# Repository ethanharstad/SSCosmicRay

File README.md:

SSCosmicRay
===========
[Hackaday Project Log](http://hackaday.io/project/2998-Solid-State-Cosmic-Ray-Detector)

Cosmic ray detectors are a common physics experiment and frequently flown on balloons to measure the change in cosmic ray flux with altitude.
These experiments are typically performed with off the shelf Geiger–Müller tube based detectors. G-M tubes are typically quite expensive and involve high voltages which can become difficult to manage in the near vacuum experienced with high altitude balloons.
A reverse biased photodiode can be used in much the same way as a G-M tube but with lower cost, lower voltage, almost no dead time, and the additional benefit of an output voltage proportional to the radiation energy. 

Inspired by a Maxim [application note](http://www.maximintegrated.com/en/app-notes/index.mvp/id/2236).

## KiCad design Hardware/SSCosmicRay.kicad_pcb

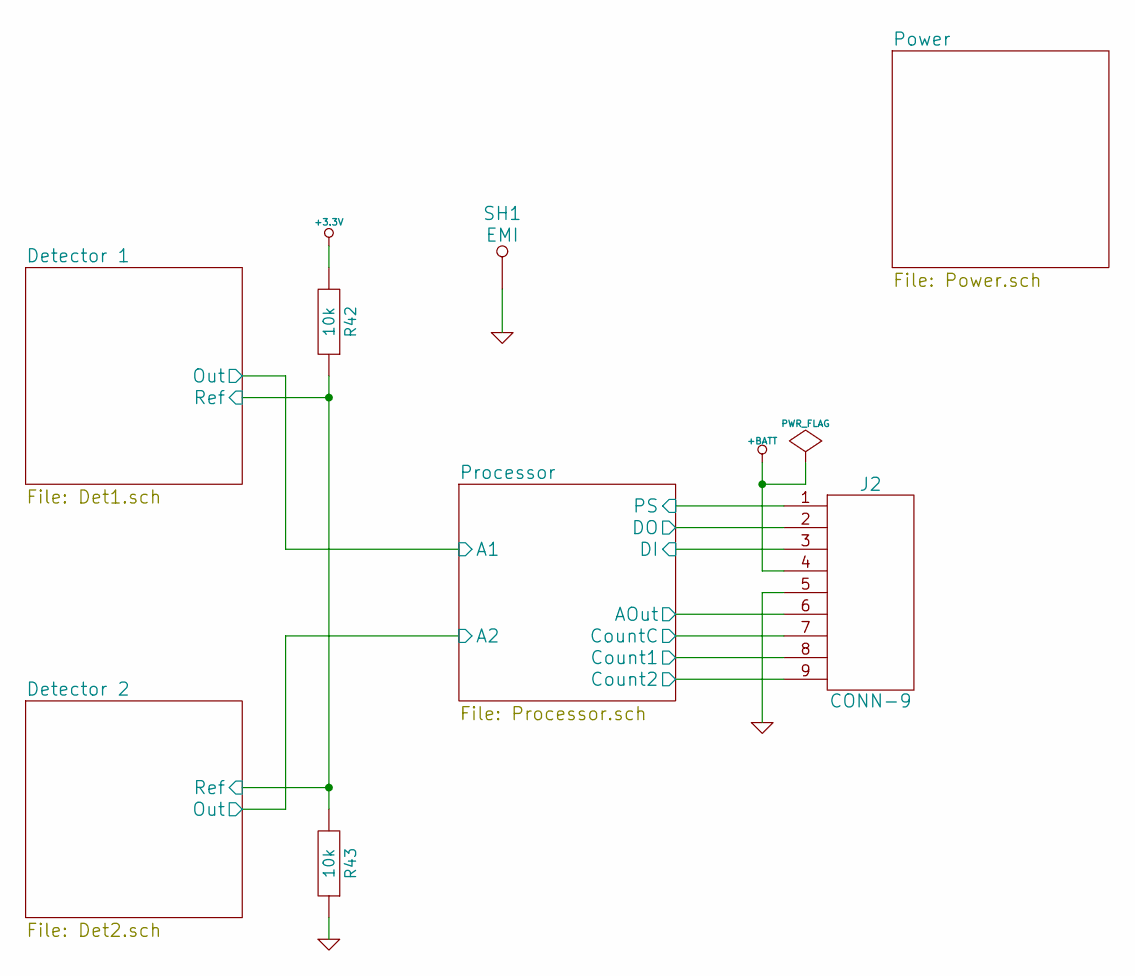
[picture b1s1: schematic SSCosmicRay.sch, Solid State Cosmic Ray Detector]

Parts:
J2: CONN-9; MFR Part No 1734354-2
R42, R43: 10k; RESC1608; Tolerance 1%; MFR Part No RC0603FR-0710KL
SH1: EMI

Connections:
+3.3V: R42.2; also elsewhere on the board
+BATT: J2.4; also elsewhere on the board
/Detector 1/Ref: R42.1, R43.2; also elsewhere on the board
/Processor/AOut: J2.6; also elsewhere on the board
/Processor/Count1: J2.8; also elsewhere on the board
/Processor/Count2: J2.9; also elsewhere on the board
/Processor/CountC: J2.7; also elsewhere on the board
/Processor/DI: J2.3; also elsewhere on the board
/Processor/DO: J2.2; also elsewhere on the board
/Processor/PS: J2.1; also elsewhere on the board
GND: J2.5, R43.1, SH1.1; also elsewhere on the board

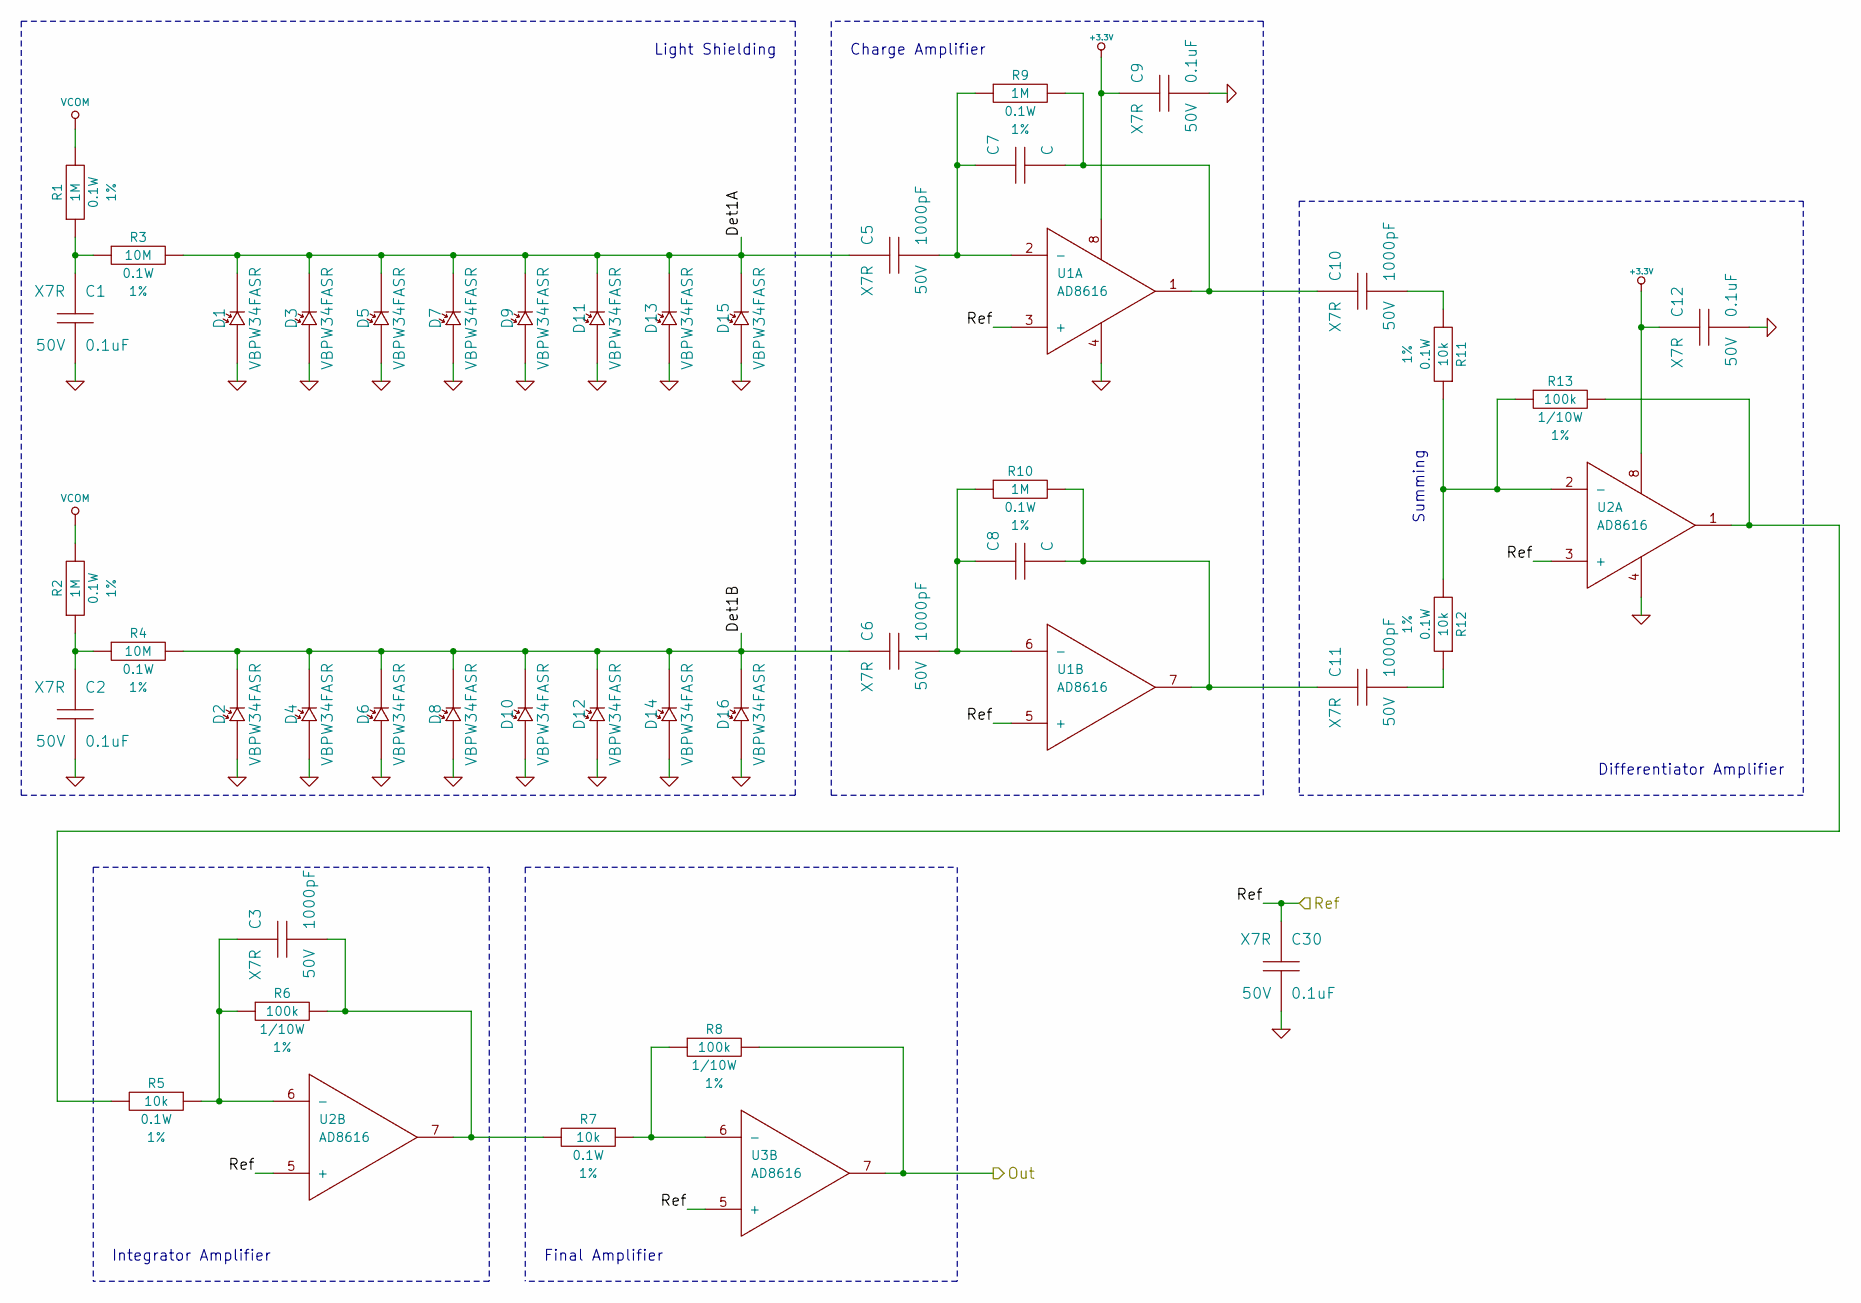
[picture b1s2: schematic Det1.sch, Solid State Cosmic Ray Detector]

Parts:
C1, C2, C9, C12, C30: 0.1uF; CAPC1608; Voltage 50V; MFR Part No CL10B104KB8SFNC
C3, C5, C6, C10, C11: 1000pF; CAPC1608; Voltage 50V; MFR Part No CL10B102KB8SFNC
C7, C8: C; Voltage V
D1, D2, D3, D4, D5, D6, D7, D8, D9, D10, D11, D12, D13, D14, D15, D16: VBPW34FASR; DIOC-BPW34R; MFR Part No VBPW34FASR
R1, R2, R9, R10: 1M; RESC1608; Tolerance 1%; MFR Part No RC0603FR-071ML
R3, R4: 10M; RESC1608; Tolerance 1%; MFR Part No RC0603FR-0710ML
R5, R7, R11, R12: 10k; RESC1608; Tolerance 1%; MFR Part No RC0603FR-0710KL
R6, R8, R13: 100k; Tolerance 1%; MFR Part No RC0603FR-07100KL
U1, U2, U3: AD8616; MFR Part No AD8616ARMZ-REEL

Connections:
+3.3V: C9.1, C12.1, U1.8, U2.8; also elsewhere on the board
/Detector 1/Det1A: C5.1, D1.2, D3.2, D5.2, D7.2, D9.2, D11.2, D13.2, D15.2, R3.2
/Detector 1/Det1B: C6.1, D2.2, D4.2, D6.2, D8.2, D10.2, D12.2, D14.2, D16.2, R4.2
/Detector 1/Ref: C30.1, U1.3 (+), U1.5 (+), U2.3 (+), U2.5 (+), U3.5 (+); also elsewhere on the board
/Processor/A1: R8.2, U3.7; also elsewhere on the board
GND: C1.2, C2.2, C9.2, C12.2, C30.2, D1.1, D2.1, D3.1, D4.1, D5.1, D6.1, D7.1, D8.1, D9.1, D10.1, D11.1, D12.1, D13.1, D14.1, D15.1, D16.1, U1.4, U2.4; also elsewhere on the board
unnamed: C8.2, C11.1, R10.2, U1.7
unnamed: C11.2, R12.1
unnamed: C10.2, R11.2
unnamed: C3.2, R6.2, R7.2, U2.7
unnamed: C7.2, C10.1, R9.2, U1.1
unnamed: R11.1, R12.2, R13.1, U2.2 (-)
unnamed: R7.1, R8.1, U3.6 (-)
unnamed: C3.1, R5.1, R6.1, U2.6 (-)
unnamed: R5.2, R13.2, U2.1
unnamed: C6.2, C8.1, R10.1, U1.6 (-)
unnamed: C5.2, C7.1, R9.1, U1.2 (-)
unnamed: C2.1, R2.1, R4.1
unnamed: C1.1, R1.1, R3.1
VCOM: R1.2, R2.2; also elsewhere on the board

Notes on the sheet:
Charge Amplifier
Differentiator Amplifier
Integrator Amplifier
Summing
Light Shielding
Final Amplifier

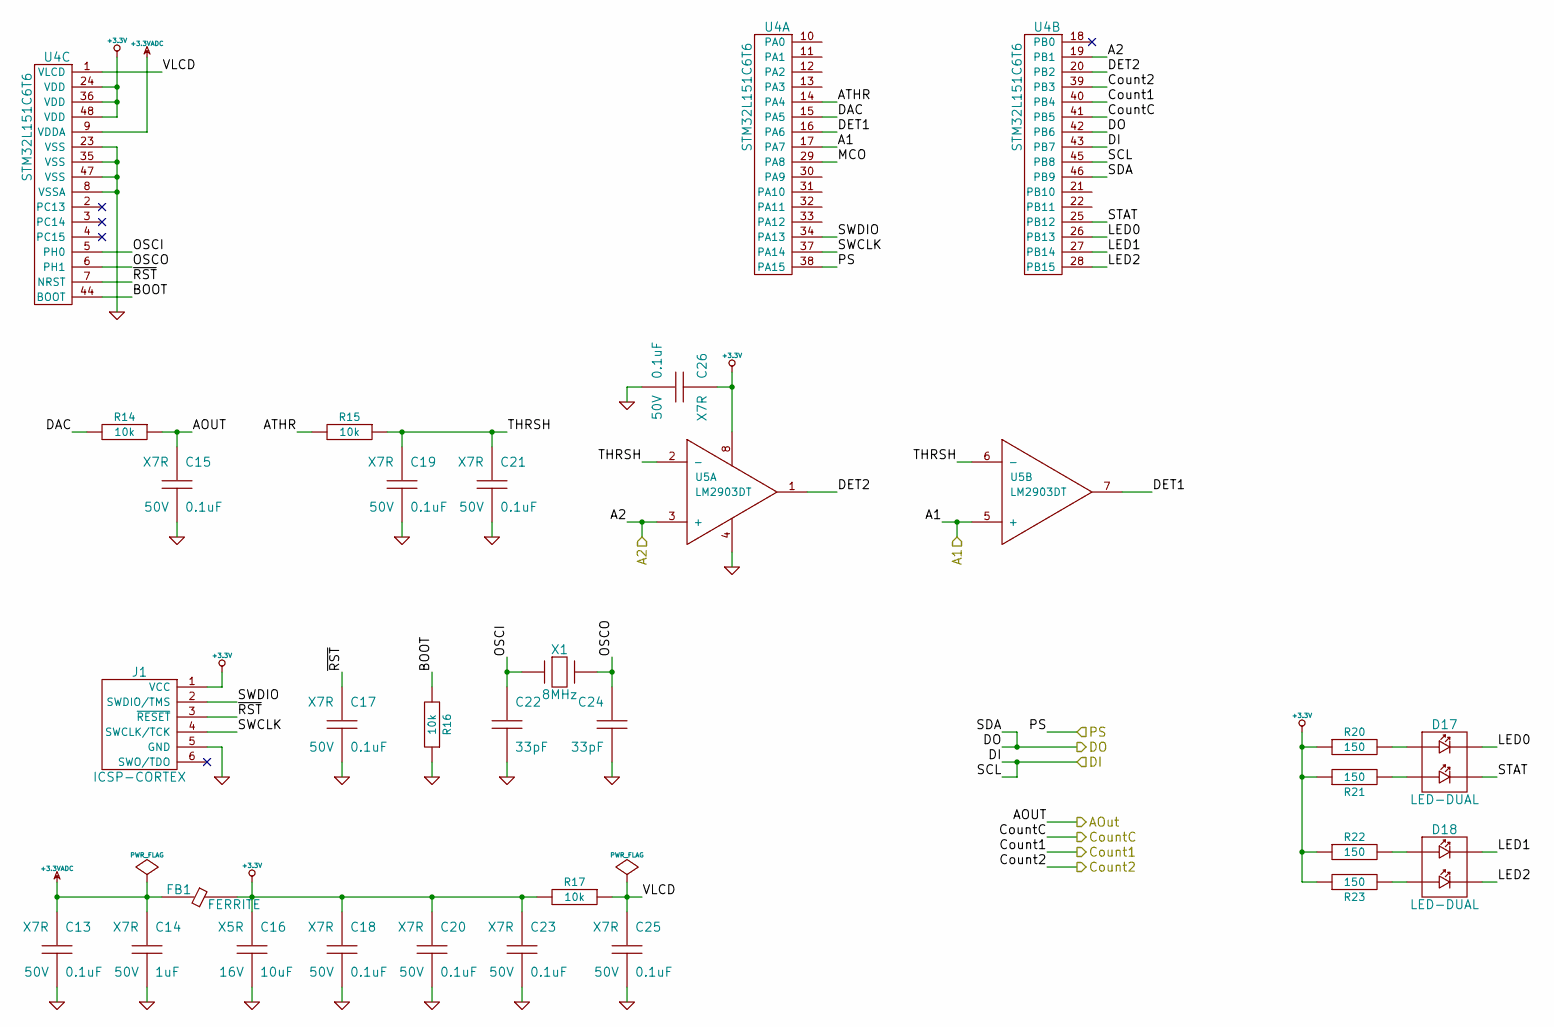
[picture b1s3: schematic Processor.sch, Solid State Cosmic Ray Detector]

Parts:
C13, C15, C17, C18, C19, C20, C21, C23, C25, C26: 0.1uF; CAPC1608; Voltage 50V; MFR Part No CL10B104KB8SFNC
C14: 1uF; CAPC1608; Voltage 50V; MFR Part No CL21B105KBFNNNE
C16: 10uF; CAPC2012; Voltage 16V; MFR Part No EMK212BJ106KG-T
C22, C24: 33pF; Voltage 50V; MFR Part No C0603C330J5GACTU
D17: LED-DUAL; Voltage V; MFR Part No 553-0121F
D18: LED-DUAL; Voltage V; MFR Part No 553-0122F
FB1: FERRITE
J1: ICSP-CORTEX
R14, R15, R16, R17: 10k; RESC1608; Tolerance 1%; MFR Part No RC0603FR-0710KL
R20, R21, R22, R23: 150; RESC1608; Tolerance %; MFR Part No RMCF0603FT150R
U4: STM32L151C6T6; MFR Part No STM32L151C6T6
U5: LM2903DT; MFR Part No LM2903DGKR
X1: 8MHz; MFR Part No ABM7-8.000MHZ-D2Y-T

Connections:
+3.3V: C16.1, C18.1, C20.1, C23.1, C26.1, FB1.2, J1.1 (VCC), R17.2, R20.1, R21.1, R22.1, R23.1, U4.24 (VDD), U4.36 (VDD), U4.48 (VDD), U5.8; also elsewhere on the board
+3.3VADC: C13.1, C14.1, FB1.1, U4.9 (VDDA)
/Processor/A1: U4.17 (PA7), U5.5 (+); also elsewhere on the board
/Processor/A2: U4.19 (PB1), U5.3 (+); also elsewhere on the board
/Processor/AOut: C15.1, R14.1; also elsewhere on the board
/Processor/ATHR: R15.2, U4.14 (PA4)
/Processor/BOOT: R16.2, U4.44 (BOOT)
/Processor/Count1: U4.40 (PB4); also elsewhere on the board
/Processor/Count2: U4.39 (PB3); also elsewhere on the board
/Processor/CountC: U4.41 (PB5); also elsewhere on the board
/Processor/DAC: R14.2, U4.15 (PA5)
/Processor/DET1: U4.16 (PA6), U5.7
/Processor/DET2: U4.20 (PB2), U5.1
/Processor/DI: U4.43 (PB7), U4.45 (PB8); also elsewhere on the board
/Processor/DO: U4.42 (PB6), U4.46 (PB9); also elsewhere on the board
/Processor/LED0: D17.2, U4.26 (PB13)
/Processor/LED1: D18.2, U4.27 (PB14)
/Processor/LED2: D18.4, U4.28 (PB15)
/Processor/OSCI: C22.1, U4.5 (PH0), X1.1
/Processor/OSCO: C24.1, U4.6 (PH1), X1.2
/Processor/PS: U4.38 (PA15); also elsewhere on the board
/Processor/STAT: D17.4, U4.25 (PB12)
/Processor/SWCLK: J1.4 (SWCLK/TCK), U4.37 (PA14)
/Processor/SWDIO: J1.2 (SWDIO/TMS), U4.34 (PA13)
/Processor/THRSH: C19.1, C21.1, R15.1, U5.2 (-), U5.6 (-)
/Processor/VLCD: C25.1, R17.1, U4.1 (VLCD)
/Processor/~RST: C17.1, J1.3 (~RESET), U4.7 (NRST)
GND: C13.2, C14.2, C15.2, C16.2, C17.2, C18.2, C19.2, C20.2, C21.2, C22.2, C23.2, C24.2, C25.2, C26.2, J1.5 (GND), R16.1, U4.8 (VSSA), U4.23 (VSS), U4.35 (VSS), U4.47 (VSS), U5.4; also elsewhere on the board
unnamed: D18.3, R23.2
unnamed: D18.1, R22.2
unnamed: D17.3, R21.2
unnamed: D17.1, R20.2

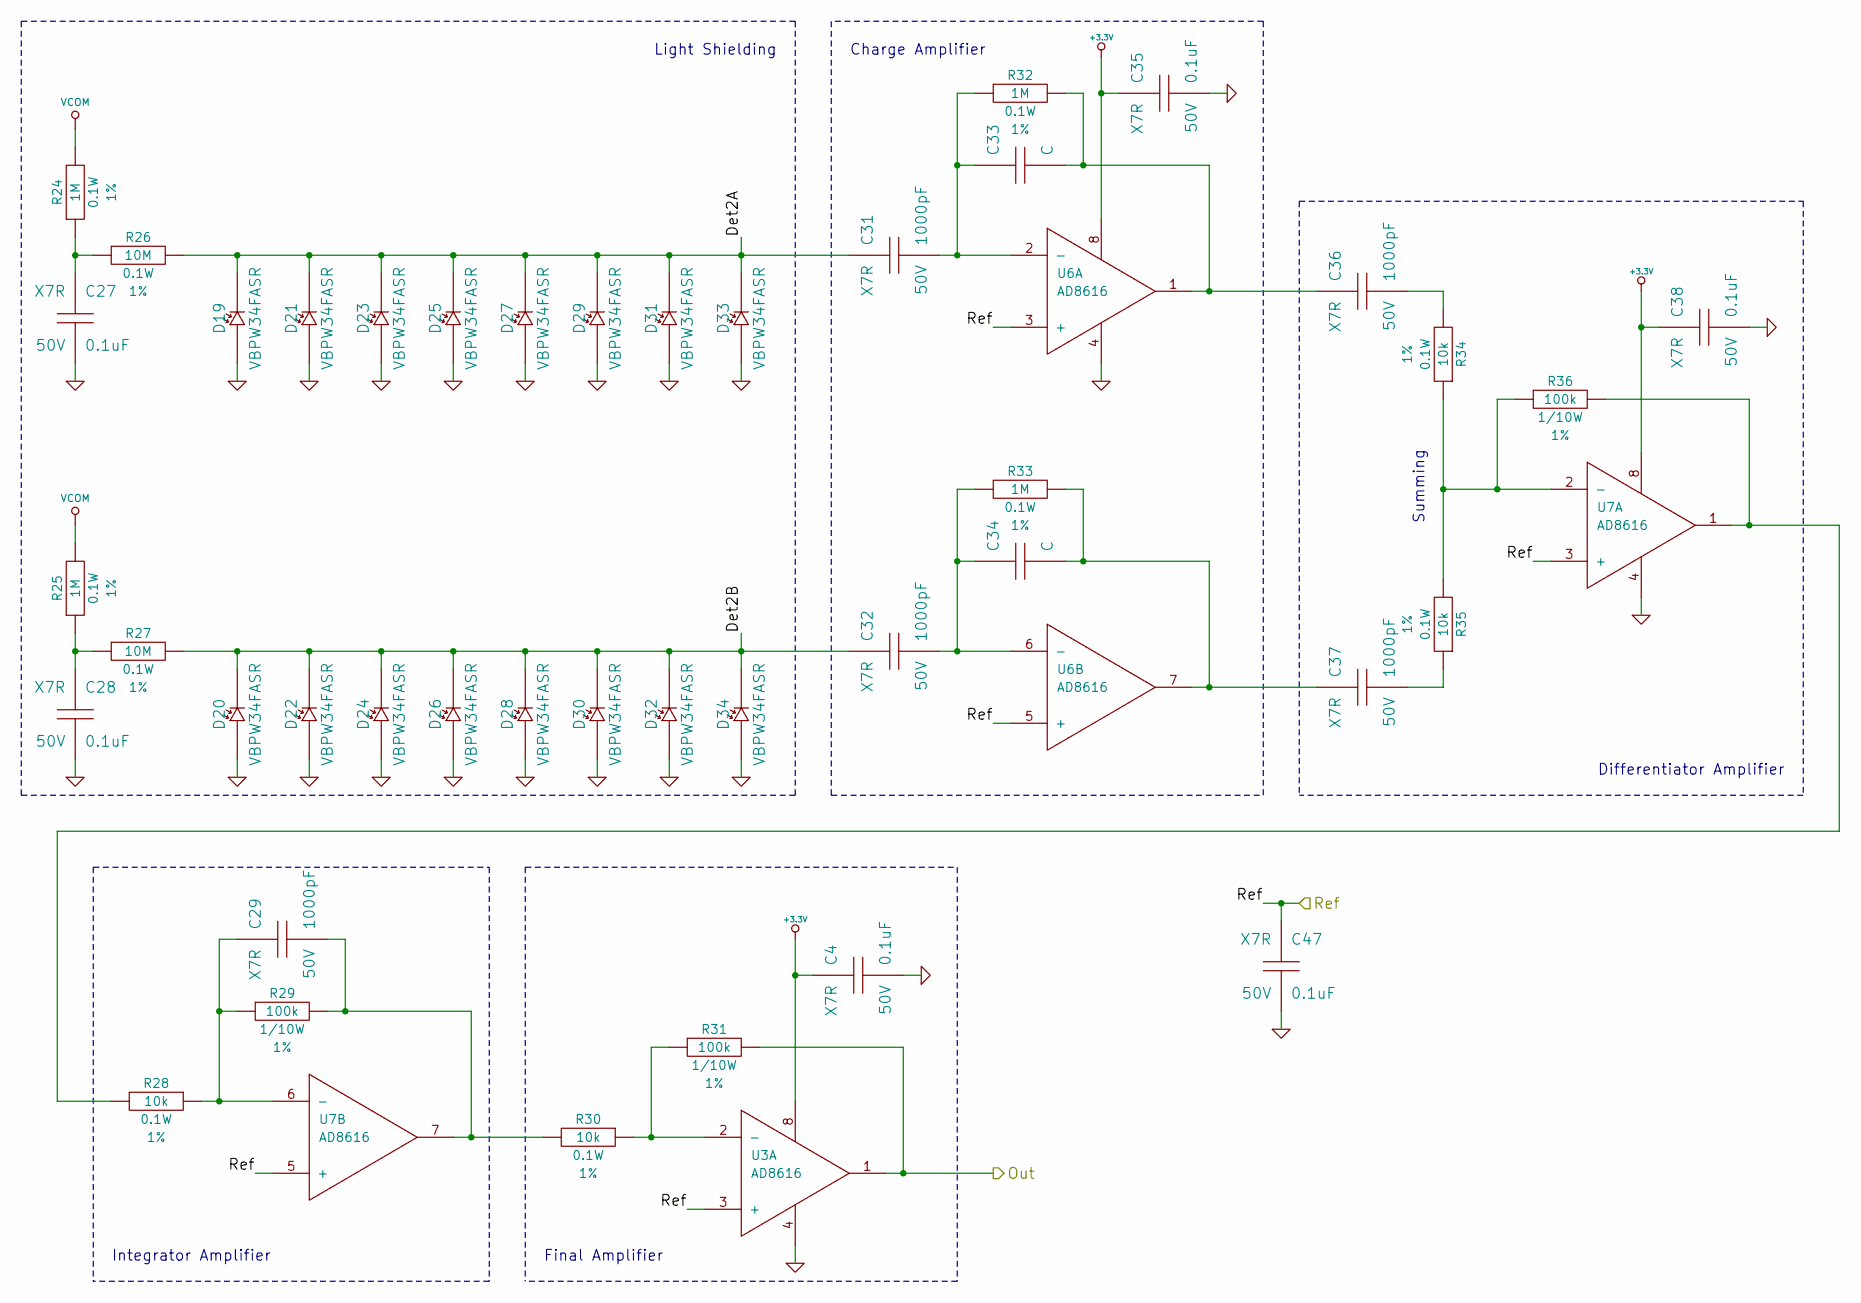
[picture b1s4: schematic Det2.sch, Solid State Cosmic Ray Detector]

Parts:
C4, C27, C28, C35, C38, C47: 0.1uF; CAPC1608; Voltage 50V; MFR Part No CL10B104KB8SFNC
C29, C31, C32, C36, C37: 1000pF; CAPC1608; Voltage 50V; MFR Part No CL10B102KB8SFNC
C33, C34: C; Voltage V
D19, D20, D21, D22, D23, D24, D25, D26, D27, D28, D29, D30, D31, D32, D33, D34: VBPW34FASR; DIOC-BPW34R; MFR Part No VBPW34FASR
R24, R25, R32, R33: 1M; RESC1608; Tolerance 1%; MFR Part No RC0603FR-071ML
R26, R27: 10M; RESC1608; Tolerance 1%; MFR Part No RC0603FR-0710ML
R28, R30, R34, R35: 10k; RESC1608; Tolerance 1%; MFR Part No RC0603FR-0710KL
R29, R31, R36: 100k; Tolerance 1%; MFR Part No RC0603FR-07100KL
U3, U6, U7: AD8616; MFR Part No AD8616ARMZ-REEL

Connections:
+3.3V: C4.1, C35.1, C38.1, U3.8, U6.8, U7.8; also elsewhere on the board
/Detector 1/Ref: C47.1, U3.3 (+), U6.3 (+), U6.5 (+), U7.3 (+), U7.5 (+); also elsewhere on the board
/Detector 2/Det2A: C31.1, D19.2, D21.2, D23.2, D25.2, D27.2, D29.2, D31.2, D33.2, R26.2
/Detector 2/Det2B: C32.1, D20.2, D22.2, D24.2, D26.2, D28.2, D30.2, D32.2, D34.2, R27.2
/Processor/A2: R31.2, U3.1; also elsewhere on the board
GND: C4.2, C27.2, C28.2, C35.2, C38.2, C47.2, D19.1, D20.1, D21.1, D22.1, D23.1, D24.1, D25.1, D26.1, D27.1, D28.1, D29.1, D30.1, D31.1, D32.1, D33.1, D34.1, U3.4, U6.4, U7.4; also elsewhere on the board
unnamed: C29.1, R28.1, R29.1, U7.6 (-)
unnamed: C37.2, R35.1
unnamed: C29.2, R29.2, R30.2, U7.7
unnamed: C34.2, C37.1, R33.2, U6.7
unnamed: R28.2, R36.2, U7.1
unnamed: C32.2, C34.1, R33.1, U6.6 (-)
unnamed: C36.2, R34.2
unnamed: R34.1, R35.2, R36.1, U7.2 (-)
unnamed: R30.1, R31.1, U3.2 (-)
unnamed: C33.2, C36.1, R32.2, U6.1
unnamed: C31.2, C33.1, R32.1, U6.2 (-)
unnamed: C28.1, R25.1, R27.1
unnamed: C27.1, R24.1, R26.1
VCOM: R24.2, R25.2; also elsewhere on the board

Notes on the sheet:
Charge Amplifier
Differentiator Amplifier
Integrator Amplifier
Summing
Light Shielding
Final Amplifier

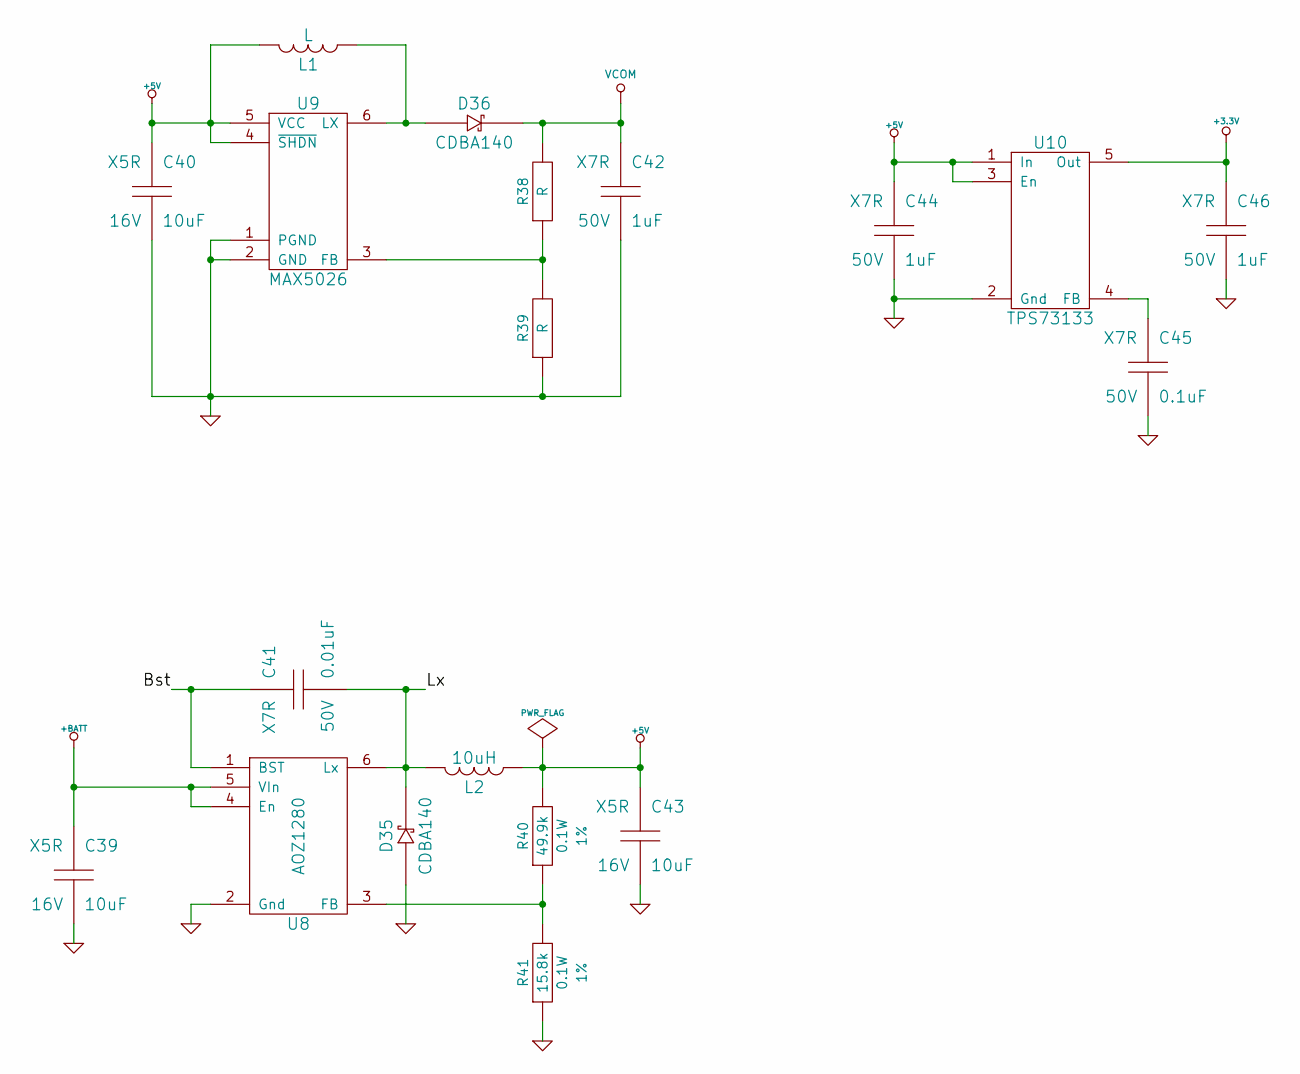
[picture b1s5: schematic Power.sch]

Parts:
C39, C40, C43: 10uF; Voltage 16V; MFR Part No EMK212BJ106KG-T
C41: 0.01uF; CAPC1608; Voltage 50V; MFR Part No CL10B103KB8NCNC
C42, C44, C46: 1uF; CAPC1608; Voltage 50V; MFR Part No CL21B105KBFNNNE
C45: 0.1uF; CAPC1608; Voltage 50V; MFR Part No CL10B104KB8SFNC
D35, D36: CDBA140; MFR Part No CDBA140-G
L1: L
L2: 10uH; INDC3225; MFR Part No CBC3225T100MR
R38, R39: R; Tolerance %
R40: 49.9k; RESC1608; Tolerance 1%; MFR Part No RC0603FR-0749K9L
R41: 15.8k; RESC1608; Tolerance 1%; MFR Part No RC0603FR-0715K8L
U8: AOZ1280; MFR Part No AOZ1280CI
U9: MAX5026; MFR Part No MAX5026EUT+T
U10: TPS73133; MFR Part No TPS73133DBVR

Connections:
+3.3V: C46.1, U10.5 (Out); also elsewhere on the board
+5V: C40.1, C43.1, C44.1, L1.1, L2.2, R40.2, U9.4 (~SHDN), U9.5 (VCC), U10.1 (In), U10.3 (En)
+BATT: C39.1, U8.4 (En), U8.5 (VIn); also elsewhere on the board
/Power/Bst: C41.1, U8.1 (BST)
/Power/Lx: C41.2, D35.2, L2.1, U8.6 (Lx)
GND: C39.2, C40.2, C42.2, C43.2, C44.2, C45.2, C46.2, D35.1, R39.1, R41.1, U8.2 (Gnd), U9.1 (PGND), U9.2 (GND), U10.2 (Gnd); also elsewhere on the board
unnamed: C45.1, U10.4 (FB)
unnamed: R38.1, R39.2, U9.3 (FB)
unnamed: R40.1, R41.2, U8.3 (FB)
unnamed: D36.1, L1.2, U9.6 (LX)
VCOM: C42.1, D36.2, R38.2; also elsewhere on the board

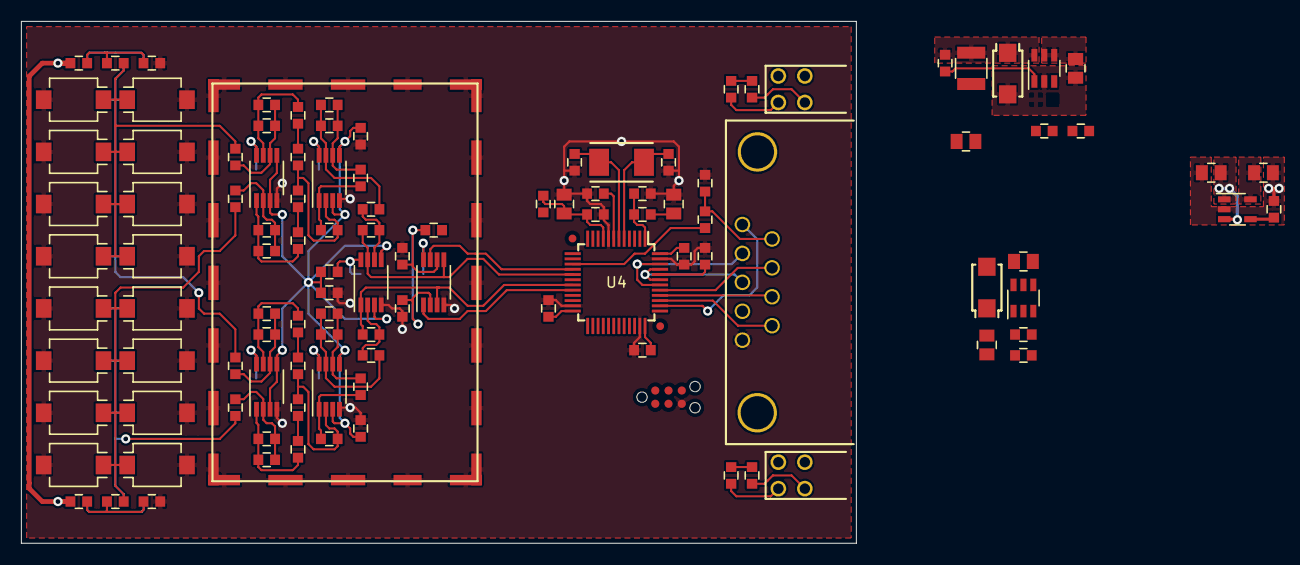
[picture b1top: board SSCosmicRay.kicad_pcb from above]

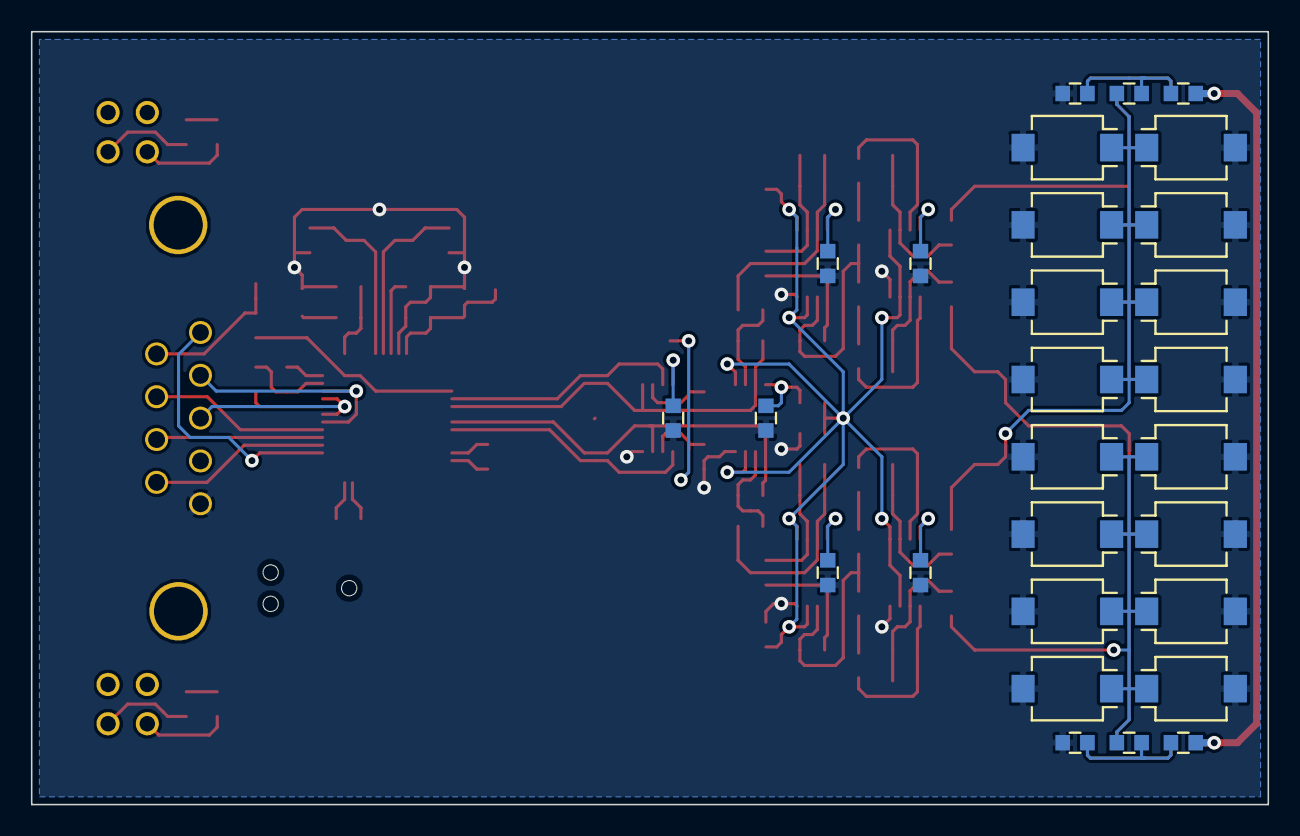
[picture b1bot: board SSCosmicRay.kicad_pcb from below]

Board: 2 copper layers, 80.0 x 50.0 mm, 139 parts (28 on the bottom side), 72 nets.

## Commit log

2013-09-20 Add amplifier signal chain
2013-09-21 Switch to hierarchical schematic, add detector section
2013-09-23 Add detector and coincidence sections
2013-09-24 Add processor section
2013-09-24 Add processor support circuitry
2013-09-24 Fill BOM fields of amplifier section
2013-09-24 Update gitignore for autosave files
2013-09-24 Fill BOM fields for detector section
2013-09-24 Fill BOM fields for coincidence section
2013-09-24 Add second detection chain
2013-09-24 Initial annotation
2013-09-24 Initial netlist
2013-09-24 Initial component mapping
2013-09-24 Map test points
2013-09-24 Fix pinout problem on potentiometer
2013-09-24 Switch analog chain to 3.3v supply
2013-09-24 Update gitignore for kicad temp files
2013-09-26 Add power section. Switch to smaller pot
2013-09-26 Associate switches
2013-09-27 Add 12v regulator and populate BOM fields
2013-09-27 Add 3.3v regulator and populate BOM fields
2013-12-06 Refresh footprints to IPC compliant versions
2013-12-07 Reroute signal chain with IPC spacing
2013-12-08 Power sections
2013-12-08 Reannotate
2013-12-08 Switch to larger enclosure
2013-12-19 Fully route signal chain
2013-12-21 Switch to 44 pin PIC
2013-12-21 Add external connector
2013-12-21 Change bias supply to reference layout
2013-12-22 Change to vertical USB port
2013-12-22 Add additional photodiodes
2013-12-22 Add status LEDs
2013-12-24 Connect LEDs
2013-12-24 Remove coincidence circuitry
    PIC32 internal comparator has sufficient performance
2013-12-24 Move amplifiers into detection subsheets
    Reannotate
2013-12-26 New signal chain layout
2013-12-27 Add shielding fingers to bottom of board
2014-01-04 Additional layout
2014-09-07 Remove old processor
    Supports #1
2014-09-07 Remove extra circuitry
2014-09-07 Update components
2014-09-11 Processor support circuitry
2014-09-11 Component associations
2014-09-11 Rough layout processor support components
2014-09-11 Add threshold detector
2014-09-11 Change DB9 to in stock part
2014-09-11 Add filter to DAC output
2014-09-11 Serial IO connections
2014-09-11 EDRC checking
2014-09-11 Change output pinout
2014-09-12 Add description and project log links
2014-09-12 Add notes
2014-09-12 Fix notes formatting
2014-09-12 Photodiode datasheet
2014-09-12 Buck regulator datasheet
2014-09-12 Replace comparator with SSOP version
    Closes #3
2014-09-22 Replace boost converter
    Closes #4
2014-09-22 Clear board, associations and annotations
    Prepare for new topology
2014-09-22 Clear annotations
2014-09-23 Add op amp datasheet
2014-09-23 Add LDO for analog
2014-09-23 LDO datasheet
2014-09-23 New detector chain
2014-09-23 Rearrange detector chain
2014-09-24 Component values
2014-09-24 Add second detector chain
2014-09-25 Change to STM32L151C
    Closes #7
2014-09-25 Swap to higher voltage 1u cap
2014-09-26 Annotate/associate most components
2014-09-28 Rough layout for pin map testing
2014-09-29 Add opamp reference voltage
2014-09-29 Change comparator label for better routing
2014-09-29 Equalize feedback network spacing
2014-09-29 Move interface connector to root sheet
2014-10-29 Input voltage preregulation to extend input range
    Closes #8
2014-11-02 Connect interface pins
2014-11-03 Route 3v3 regulator
2014-11-18 Routing
2014-11-18 Remove discrete pull-ups in favor of on chip pull-ups
2014-11-28 Remove unneeded pullup on regulator enable
